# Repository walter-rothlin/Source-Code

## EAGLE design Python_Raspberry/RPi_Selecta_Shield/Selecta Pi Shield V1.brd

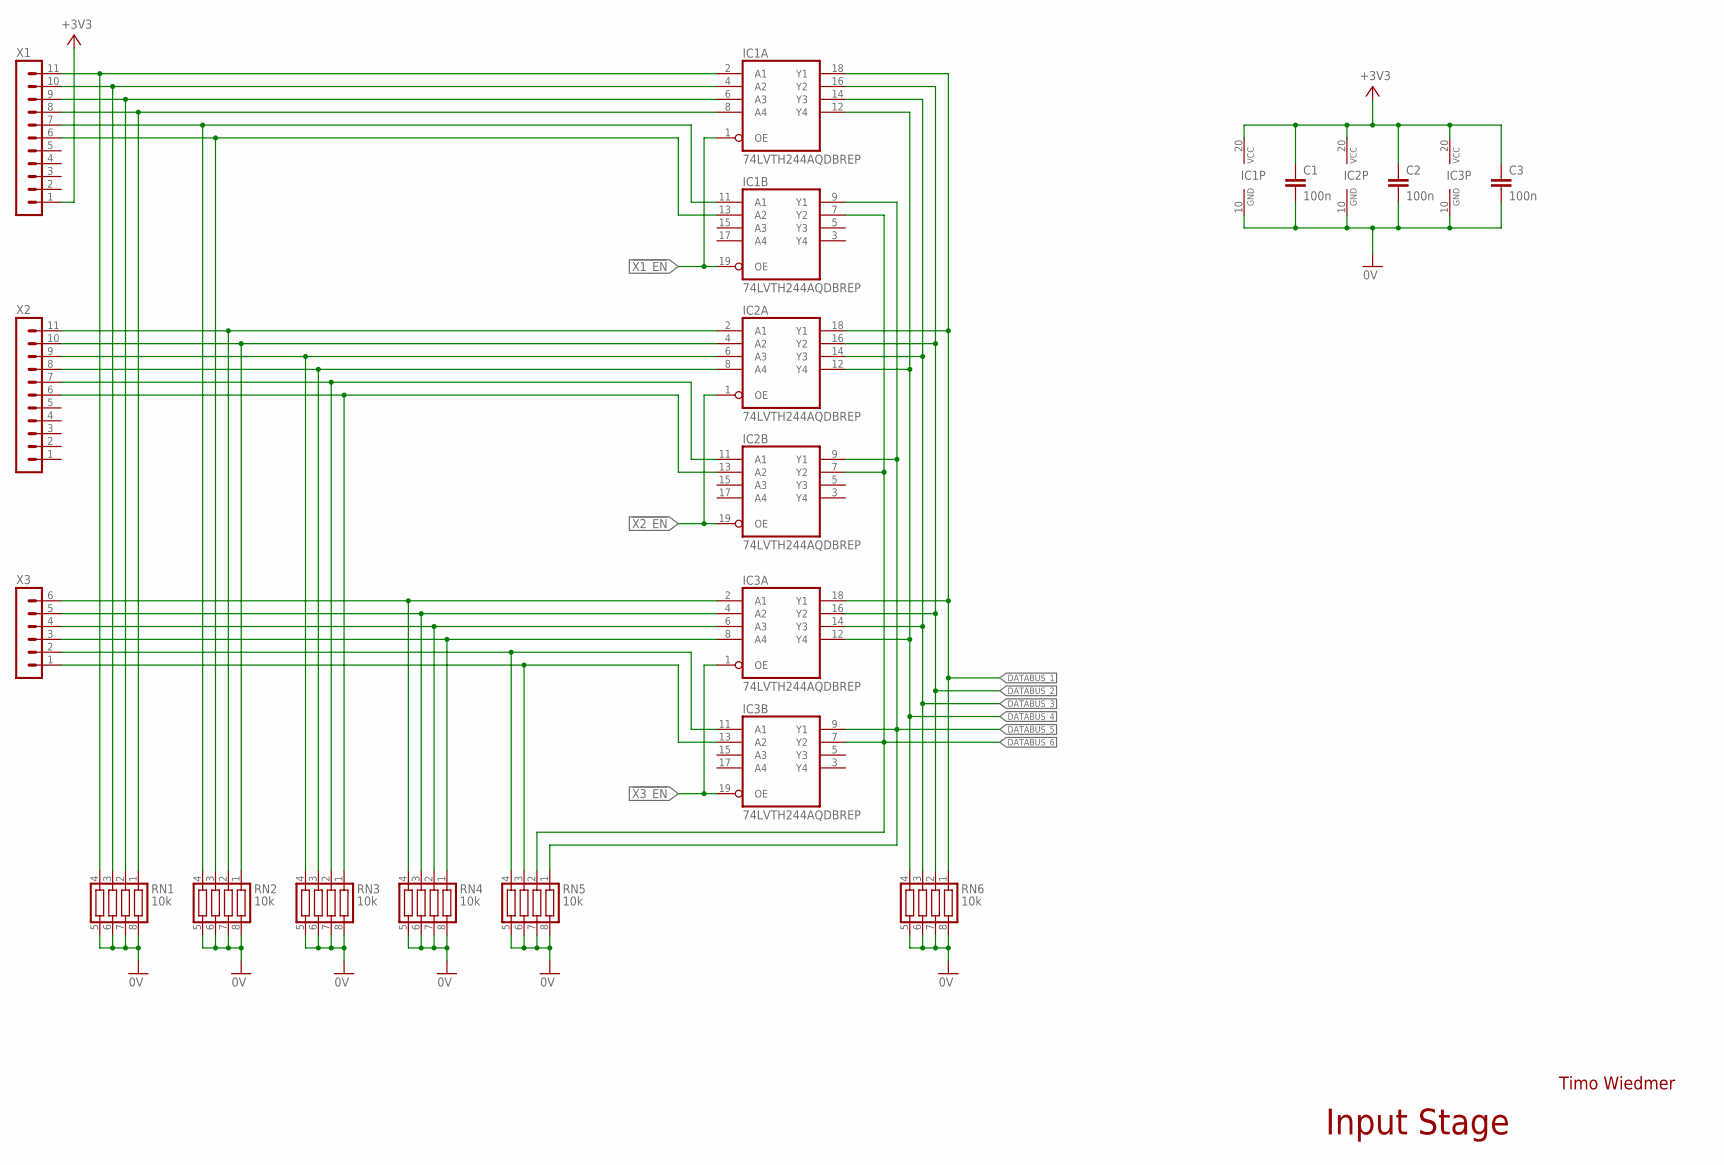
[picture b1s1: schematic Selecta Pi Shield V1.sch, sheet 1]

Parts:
C1, C2, C3: 100n; C0603
IC1, IC2, IC3: 74LVTH244AQDBREP; SSOP20
RN1, RN2, RN3, RN4, RN5, RN6: 10k; CTS742C083
X1, X2: MA11-1
X3: MA06-1

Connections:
0V: C1.2, C2.2, C3.2, IC1.10 (GND), IC2.10 (GND), IC3.10 (GND), RN1.5, RN1.6, RN1.7, RN1.8, RN2.5, RN2.6, RN2.7, RN2.8, RN3.5, RN3.6, RN3.7, RN3.8, RN4.5, RN4.6, RN4.7, RN4.8, RN5.5, RN5.6, RN5.7, RN5.8, RN6.5, RN6.6, RN6.7, RN6.8; also elsewhere on the board
!X1_EN: IC1.1 (OE), IC1.19 (OE); also elsewhere on the board
!X2_EN: IC2.1 (OE), IC2.19 (OE); also elsewhere on the board
!X3_EN: IC3.1 (OE), IC3.19 (OE); also elsewhere on the board
+3V3: C1.1, C2.1, C3.1, IC1.20 (VCC), IC2.20 (VCC), IC3.20 (VCC), X1.1; also elsewhere on the board
DATABUS_1: IC1.18 (Y1), IC2.18 (Y1), IC3.18 (Y1), RN6.1; also elsewhere on the board
DATABUS_2: IC1.16 (Y2), IC2.16 (Y2), IC3.16 (Y2), RN6.2; also elsewhere on the board
DATABUS_3: IC1.14 (Y3), IC2.14 (Y3), IC3.14 (Y3), RN6.3; also elsewhere on the board
DATABUS_4: IC1.12 (Y4), IC2.12 (Y4), IC3.12 (Y4), RN6.4; also elsewhere on the board
DATABUS_5: IC1.9 (Y1), IC2.9 (Y1), IC3.9 (Y1), RN5.1; also elsewhere on the board
DATABUS_6: IC1.7 (Y2), IC2.7 (Y2), IC3.7 (Y2), RN5.2; also elsewhere on the board
unnamed: IC1.2 (A1), RN1.4, X1.11
unnamed: IC1.4 (A2), RN1.3, X1.10
unnamed: IC1.6 (A3), RN1.2, X1.9
unnamed: IC1.8 (A4), RN1.1, X1.8
unnamed: IC2.2 (A1), RN2.2, X2.11
unnamed: IC2.4 (A2), RN2.1, X2.10
unnamed: IC2.6 (A3), RN3.4, X2.9
unnamed: IC2.8 (A4), RN3.3, X2.8
unnamed: IC3.2 (A1), RN4.4, X3.6
unnamed: IC3.4 (A2), RN4.3, X3.5
unnamed: IC1.11 (A1), RN2.4, X1.7
unnamed: IC1.13 (A2), RN2.3, X1.6
unnamed: IC2.11 (A1), RN3.2, X2.7
unnamed: IC3.6 (A3), RN4.2, X3.4
unnamed: IC2.13 (A2), RN3.1, X2.6
unnamed: IC3.8 (A4), RN4.1, X3.3
unnamed: IC3.11 (A1), RN5.4, X3.2
unnamed: IC3.13 (A2), RN5.3, X3.1

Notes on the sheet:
Timo Wiedmer
Input Stage

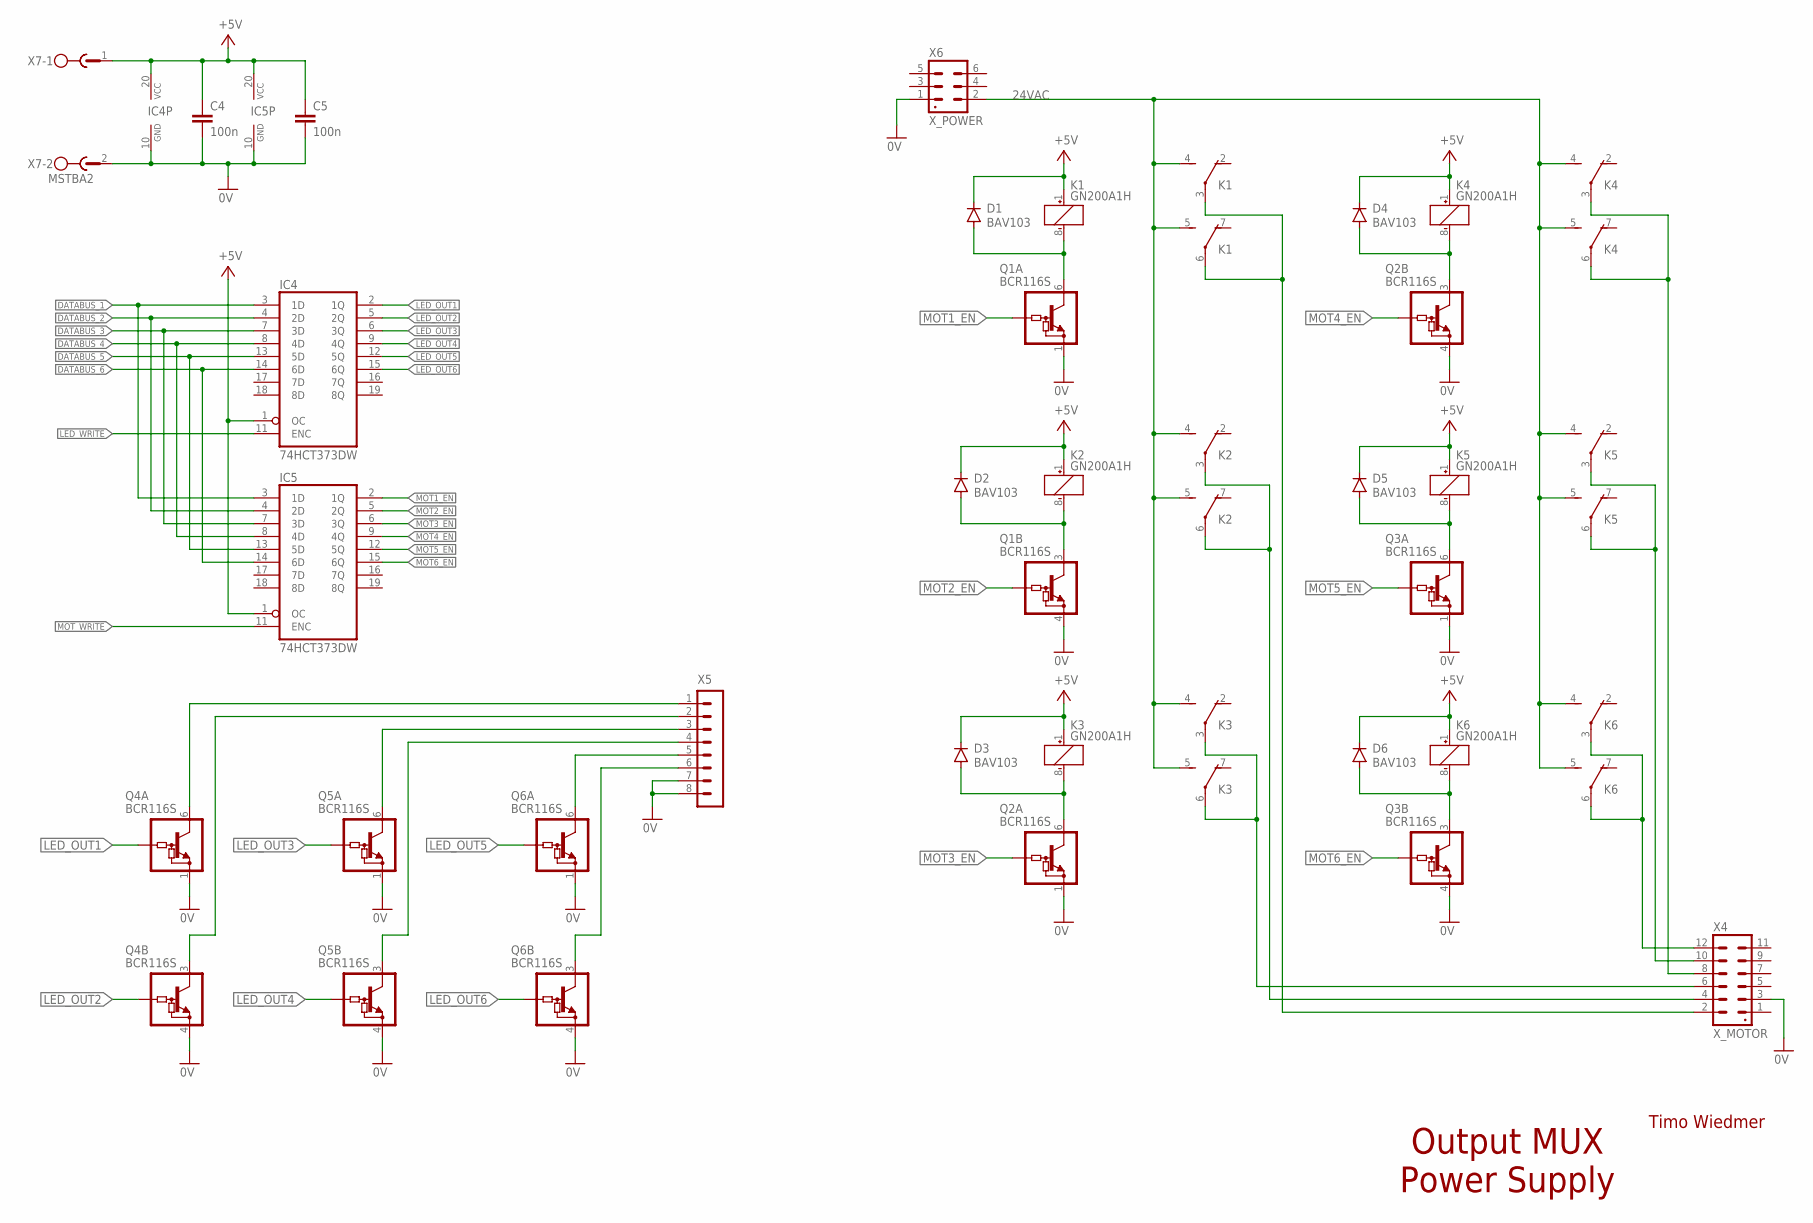
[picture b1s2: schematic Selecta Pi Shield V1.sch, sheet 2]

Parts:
C4, C5: 100n; C0603
D1, D2, D3, D4, D5, D6: BAV103; SOD-123_MINI-SMA
IC4, IC5: 74HCT373DW; SO20W
K1, K2, K3, K4, K5, K6: GN200A1H; GN-A
Q1, Q2, Q3, Q4, Q5, Q6: BCR116S; SOT363
X4: X_MOTOR; 12P_MINI_FIT
X5: MA08-1
X6: X_POWER; 6P_MINI_FIT
X7: MSTBA2

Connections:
0V: C4.2, C5.2, IC4.10 (GND), IC5.10 (GND), Q1.1 (E), Q1.4 (E), Q2.1 (E), Q2.4 (E), Q3.1 (E), Q3.4 (E), Q4.1 (E), Q4.4 (E), Q5.1 (E), Q5.4 (E), Q6.1 (E), Q6.4 (E), X4.3, X5.7, X5.8, X6.1, X7.2; also elsewhere on the board
24VAC: K1.4 (S), K1.5 (S), K2.4 (S), K2.5 (S), K3.4 (S), K3.5 (S), K4.4 (S), K4.5 (S), K5.4 (S), K5.5 (S), K6.4 (S), K6.5 (S), X6.2
24VAC_MOT1: K1.3, K1.6, X4.2
24VAC_MOT2: K2.3, K2.6, X4.4
24VAC_MOT3: K3.3, K3.6, X4.6
24VAC_MOT4: K4.3, K4.6, X4.8
24VAC_MOT5: K5.3, K5.6, X4.10
24VAC_MOT6: K6.3, K6.6, X4.12
+5V: C4.1, C5.1, D1.C, D2.C, D3.C, D4.C, D5.C, D6.C, IC4.1 (OC), IC4.20 (VCC), IC5.1 (OC), IC5.20 (VCC), K1.1 (+), K2.1 (+), K3.1 (+), K4.1 (+), K5.1 (+), K6.1 (+), X7.1; also elsewhere on the board
DATABUS_1: IC4.3 (1D), IC5.3 (1D); also elsewhere on the board
DATABUS_2: IC4.4 (2D), IC5.4 (2D); also elsewhere on the board
DATABUS_3: IC4.7 (3D), IC5.7 (3D); also elsewhere on the board
DATABUS_4: IC4.8 (4D), IC5.8 (4D); also elsewhere on the board
DATABUS_5: IC4.13 (5D), IC5.13 (5D); also elsewhere on the board
DATABUS_6: IC4.14 (6D), IC5.14 (6D); also elsewhere on the board
LED_OUT1: IC4.2 (1Q), Q4.2 (B)
LED_OUT2: IC4.5 (2Q), Q4.5 (B)
LED_OUT3: IC4.6 (3Q), Q5.2 (B)
LED_OUT4: IC4.9 (4Q), Q5.5 (B)
LED_OUT5: IC4.12 (5Q), Q6.2 (B)
LED_OUT6: IC4.15 (6Q), Q6.5 (B)
LED_WRITE: IC4.11 (ENC); also elsewhere on the board
MOT1_EN: IC5.2 (1Q), Q1.2 (B)
MOT2_EN: IC5.5 (2Q), Q1.5 (B)
MOT3_EN: IC5.6 (3Q), Q2.2 (B)
MOT4_EN: IC5.9 (4Q), Q2.5 (B)
MOT5_EN: IC5.12 (5Q), Q3.2 (B)
MOT6_EN: IC5.15 (6Q), Q3.5 (B)
MOT_WRITE: IC5.11 (ENC); also elsewhere on the board
unnamed: Q4.6 (C), X5.1
unnamed: Q4.3 (C), X5.2
unnamed: D3.A, K3.8 (-), Q2.6 (C)
unnamed: D6.A, K6.8 (-), Q3.3 (C)
unnamed: D5.A, K5.8 (-), Q3.6 (C)
unnamed: D2.A, K2.8 (-), Q1.3 (C)
unnamed: D1.A, K1.8 (-), Q1.6 (C)
unnamed: D4.A, K4.8 (-), Q2.3 (C)
unnamed: Q5.6 (C), X5.3
unnamed: Q5.3 (C), X5.4
unnamed: Q6.6 (C), X5.5
unnamed: Q6.3 (C), X5.6

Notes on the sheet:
Timo Wiedmer
Output MUX Power Supply

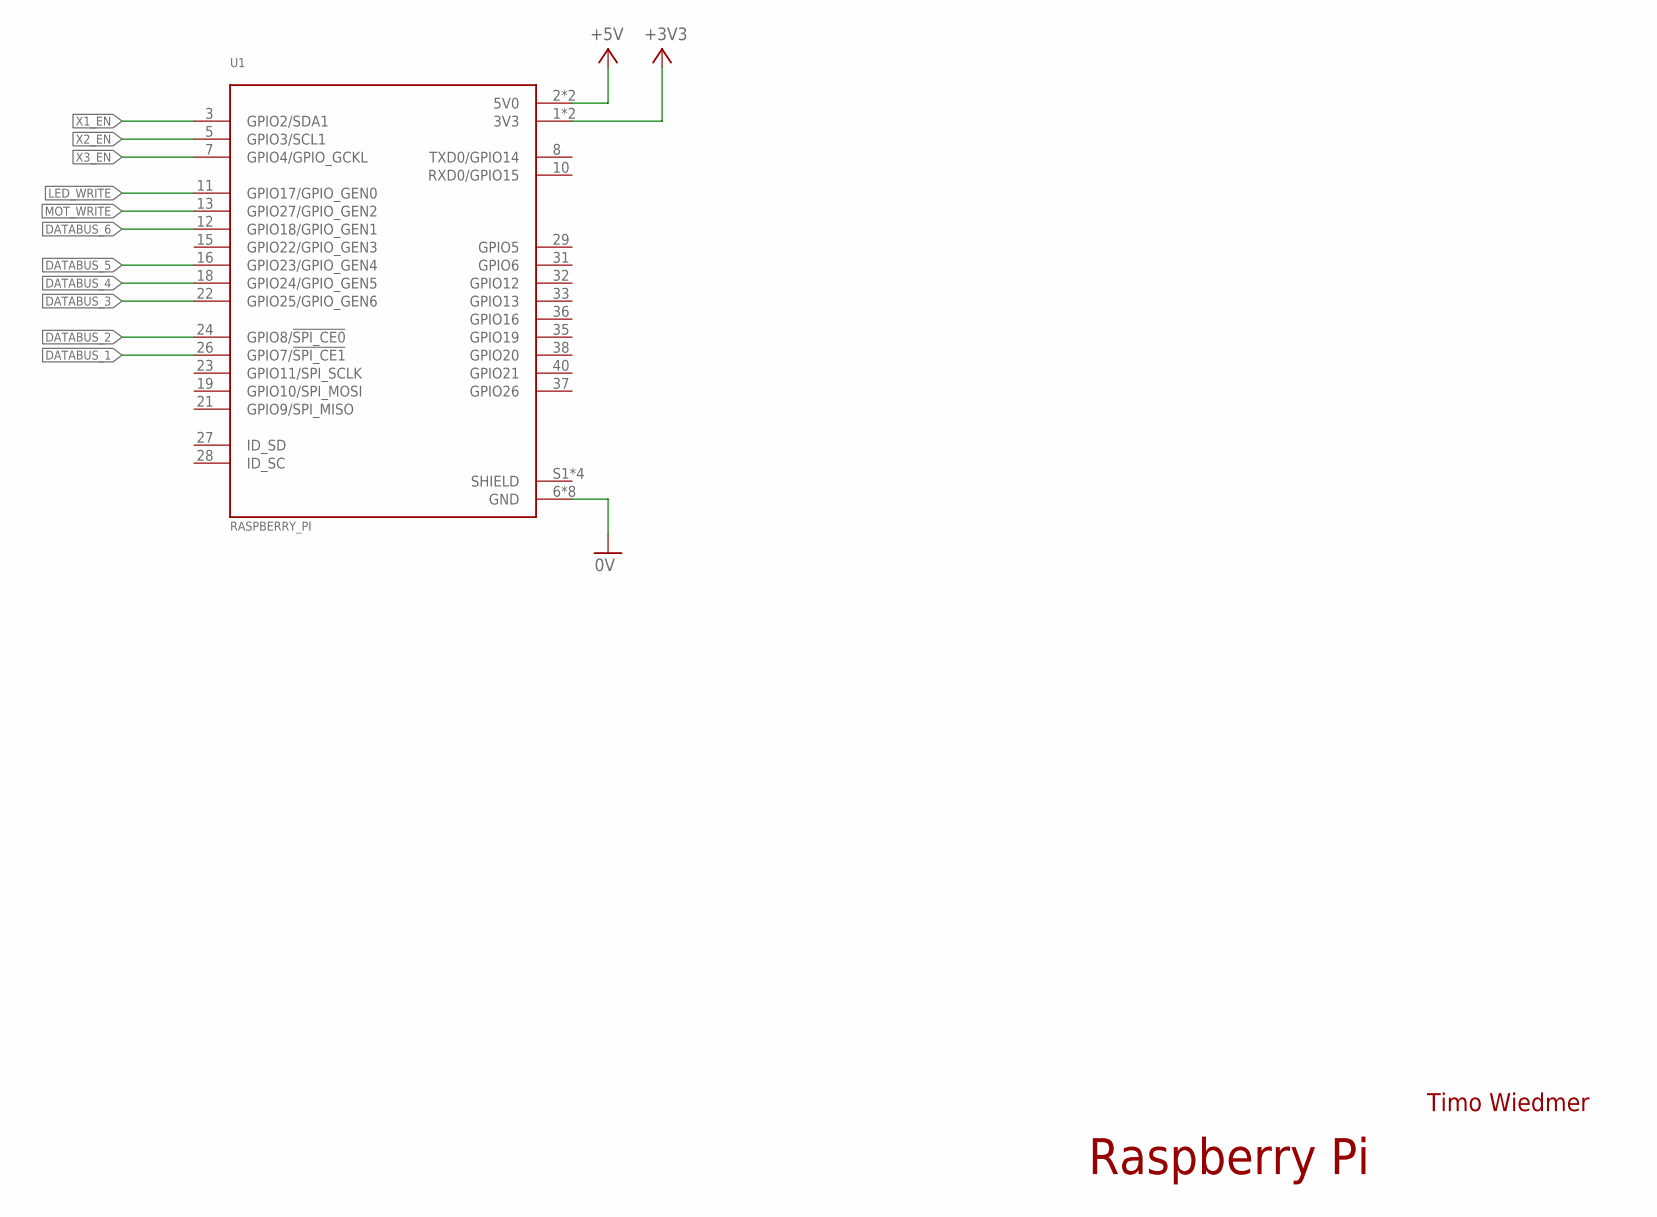
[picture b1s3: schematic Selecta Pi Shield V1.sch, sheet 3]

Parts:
U1: RASPBERRY_PI

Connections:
0V: U1.6 (GND), U1.9 (GND), U1.14 (GND), U1.20 (GND), U1.25 (GND), U1.30 (GND), U1.34 (GND), U1.39 (GND); also elsewhere on the board
!X1_EN: U1.3 (GPIO2/SDA1); also elsewhere on the board
!X2_EN: U1.5 (GPIO3/SCL1); also elsewhere on the board
!X3_EN: U1.7 (GPIO4/GPIO_GCKL); also elsewhere on the board
+3V3: U1.1 (3V3), U1.17 (3V3); also elsewhere on the board
+5V: U1.2 (5V0), U1.4 (5V0); also elsewhere on the board
DATABUS_1: U1.26 (GPIO7/!SPI_CE1!); also elsewhere on the board
DATABUS_2: U1.24 (GPIO8/!SPI_CE0!); also elsewhere on the board
DATABUS_3: U1.22 (GPIO25/GPIO_GEN6); also elsewhere on the board
DATABUS_4: U1.18 (GPIO24/GPIO_GEN5); also elsewhere on the board
DATABUS_5: U1.16 (GPIO23/GPIO_GEN4); also elsewhere on the board
DATABUS_6: U1.12 (GPIO18/GPIO_GEN1); also elsewhere on the board
LED_WRITE: U1.11 (GPIO17/GPIO_GEN0); also elsewhere on the board
MOT_WRITE: U1.13 (GPIO27/GPIO_GEN2); also elsewhere on the board
SHIELD: U1.S1 (SHIELD), U1.S2 (SHIELD), U1.S3 (SHIELD), U1.S4 (SHIELD)

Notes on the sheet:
Timo Wiedmer
Raspberry Pi

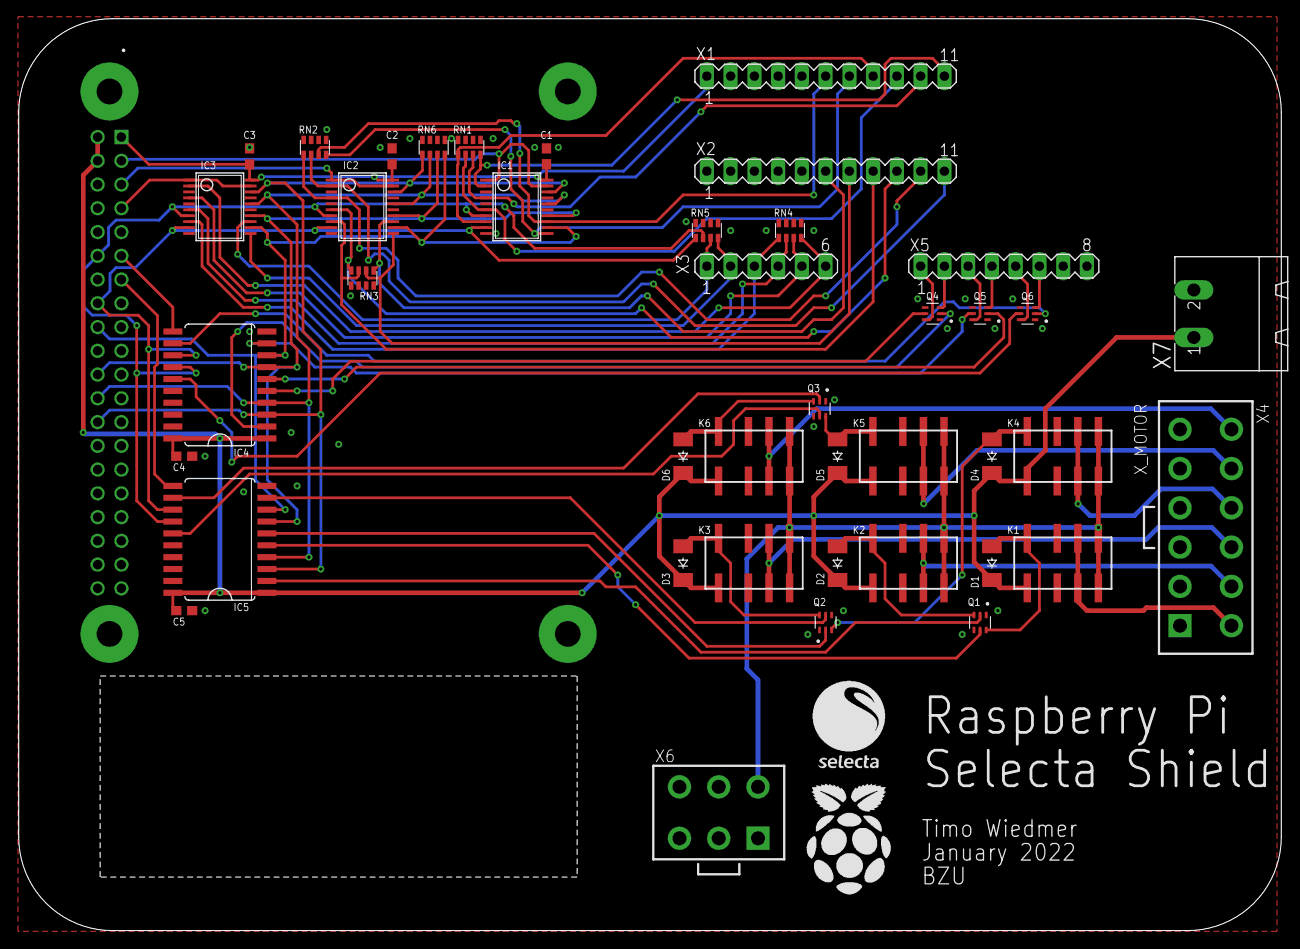
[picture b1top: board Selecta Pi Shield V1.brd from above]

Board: 2 copper layers, 135.0 x 97.5 mm, 44 parts (0 on the bottom side), 64 nets.

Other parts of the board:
U$1: RASPBERRY_LOGO
U$2: SELECTA_LOGO

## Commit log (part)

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2023-06-22 Gelöscht
2023-07-02 Uopdate
2023-09-12 Upadte
2023-09-21 Update für BZU
    Beispiel
2024-10-08 New release
2024-11-12 Upodate
2024-12-09 Move to RPi
2024-12-27 Upüdate
2025-05-08 Update after BWI-A23 test
2025-11-13 Adresslocator
2025-11-19 Update Python HFU
2025-12-22 Adress_Search
2025-12-31 BWI-A23_Web_LN
2026-03-01 HWZ Unterlagen for 2026
2026-03-01 HWZ 2026
2026-05-12 Update for BWI-A23
2026-06-03 Updated for BWI-A24
2026-06-09 Formelbuch
2026-06-22 LN_BWI_A23_Distributed
2026-06-29 Meteo-Schweiz Service included
